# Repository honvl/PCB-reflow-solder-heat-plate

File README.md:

# PCB reflow solder heat plate

## Introduction

The PCB reflow solder heat plate can be used to solder small PCBs with SMD parts. The user can control the maximum temperature and heating curve. Buy a pre-assembled version here: https://www.tindie.com/products/littlethings/pcb-reflow-soldering-hot-plate/

## Hardware design

The idea for this design comes from https://github.com/AfterEarthLTD/Solder-Reflow-Plate. But when I checked the original design, I found some issues that could cause safety problems and other design choices that are not optimal.

## Hardware version 1.2

- Removed resettable fuse which was overheating and tripping
- Increased power supply capacitor ratings to 35V for 24V power supply compatibility
- Use 2 SMD capacitors for power supply capacitors instead of 4 standard ones for lower total board height
- Changed to easier to press switches

### Feature list

- PCB size 100x100mm, heat plate size 81x69mm
- DC barrel plug (5.5x2.5mm), runs with 12V/5A power supply
- inrush current limiter to protect power supply when capacitors are discharged
- 2.7mF input power filter for smooth current draw
- capacitor discharging resistors
- ATMEGA4809 MCU, can be programmed via UPDI header
- high power NMOS with gate driver circuit
- flyback diode connected to the heat plate
- AMS1117 LDO
- additional diodes for protection
- dual buttons
- status LED
- 0.91" OLED display
- LMT85 analog temperature sensor as main sensor
- option to add additional digital sensors for calibration purposes

### Building your own

You can order almost all parts needed from LCSC/JLCPCB. Only the OLED display and the power supply need to be sourced elsewhere. The BOM includes LCSC part numbers for hand soldering and their automated SMT manufacturing. Minimal part size is 0805 and there's enough space between all solder pads, so hand soldering should be no problem if you have a steady hand. Hardest part will be the MCU, but this is hand solderable, too.

### Safety measures compared to the original design

The original design had a too low heat plate resistance, which caused very high current spikes when the heat plate was turned on. This should be filtered by PWM and the input capacitors, but the input capacitor in the original design was far too small (100µF). Because of this, the fuse always blew when the device was turned on, so eventually the fuse was removed again.
In my design I made the input capacitors 27 times larger to have a smoother current draw. I also added a fuse, and an inrush current limiter. After disconnecting the power supply, the output capacitors are quickly discharged to GND.
The original also had no gate driver, so the NMOS was only driven with logic levels. I added a simple NPN gate driver.
Switching inductive loads (like the long heat plate trace) causes voltage spikes. In the original design, the filtering was done with an ESD diode and a small capacitor. The usual way to filter these voltage spikes is a flyback diode.
The resistance of the heat plate was very low, so the current draw with 100% PWM duty cycle was very high. If the MCUs hangs up and the power MOSFET stays active, the original design could cause too much stress for the power supply. Furthermore, even with a hot heat plate, the resistance would still be so low that the board would draw more than 5A.
In my design, the heat plate resistance was chosen in a way that a hot heat plate will draw less than 5A, so it is much safer to run the new design, as it will automatically reach electrically safe working conditions.

## Firmware

The original firmware was reworked by Nathan Heidt (https://github.com/heidtn) and works mostly, only the temperature sensing is incorrect (as the firmware was written with an earlier board revision). So for now, you just need to unplug the device when the PCB that needed soldering is done. Also, the dual color LED is not yet included into the code, for now it just lights green to show power. And the buttons sometimes don't react properly.

Daniel Oltmanns (https://github.com/oltdaniel) is doing a rework of the firmware using platformio.

### To-do list for software:
- use of the dual color LED (green = power, orange = heating, red = hot)
- better temperature sensing
- better working buttons
- calibration function for the analog temperature sensor by taping a digital probe directly to the heat plate

Please note that I can only do hardware design, so I can't contribute anything to the software. 

### Programming the MCU

The MCU can be programmed with JTAG2UPDI (https://github.com/ElTangas/jtag2updi). For programming, you need an Arduino with ATMEGA328p (Uno or Nano), some wires, a 4.7k resistor and  a 10µF capacitor or 120 Ohm resistor to disable the auto-reset.

JCM from the Discord explained the process pretty good:

> 1. Download/Clone this project: https://github.com/ElTangas/jtag2updi and rename the folder "source" to "jtag2updi" (otherwise the Arduino IDE won't like it)
> 2. Open jtag2updi/jtag2updi.ino in your Arduino IDE
> 3. Configure the flasher options for your Arduino Nano and flash it
> 4. Connect D6 of your Arduino Nano over the 4.7kOhm resistor to the UPDI pin of the board and 5V to 5V and GND to 0V
> 5. Add the MegaCoreX hardware package to the Ardunio IDE (see https://github.com/MCUdude/MegaCoreX#how-to-install)
> 6. Install the Adafruit_GFX, Adafruit_SSD1306, DallasTemperature and Debounce2 libraries with the Library Manager (you might not need all of them depending on which firmware you plan to use)
> 7. Download and open the ino you want to upload to the ATMEGA4809 (https://github.com/DerSpatz/PCB-reflow-solder-heat-plate/blob/main/Firmware/pcb_reflow_fw/pcb_reflow_fw.ino)
> 8. Select the options for the programmer (Board: ATmega4809, Clock: Internal 16 MHz, BOD: 2.6V or 2.7V, EEPROM: retained, Pinout: 48 pin standard, Reset pin: Reset, no Bootloader) and select the port of your Ardunio Nano as Port
> 9. Select Burn Bootloader and see if it runs through
> 10. Temporarily disable auto reset for the Arduino Nano: https://playground.arduino.cc/Main/DisablingAutoResetOnSerialConnection/ (not sure if it's needed for the Nano, it was for my Mega)
> 11. Select Sketch > Upload using Programmer (normal Upload will not work)

## Thanks

Special Thanks go out to:

Nathan Heidt for writing the software and testing

Merlin Shaw (www.facebook.com/GeekIslandGaming) for ordering the first batch of prototypes and testing

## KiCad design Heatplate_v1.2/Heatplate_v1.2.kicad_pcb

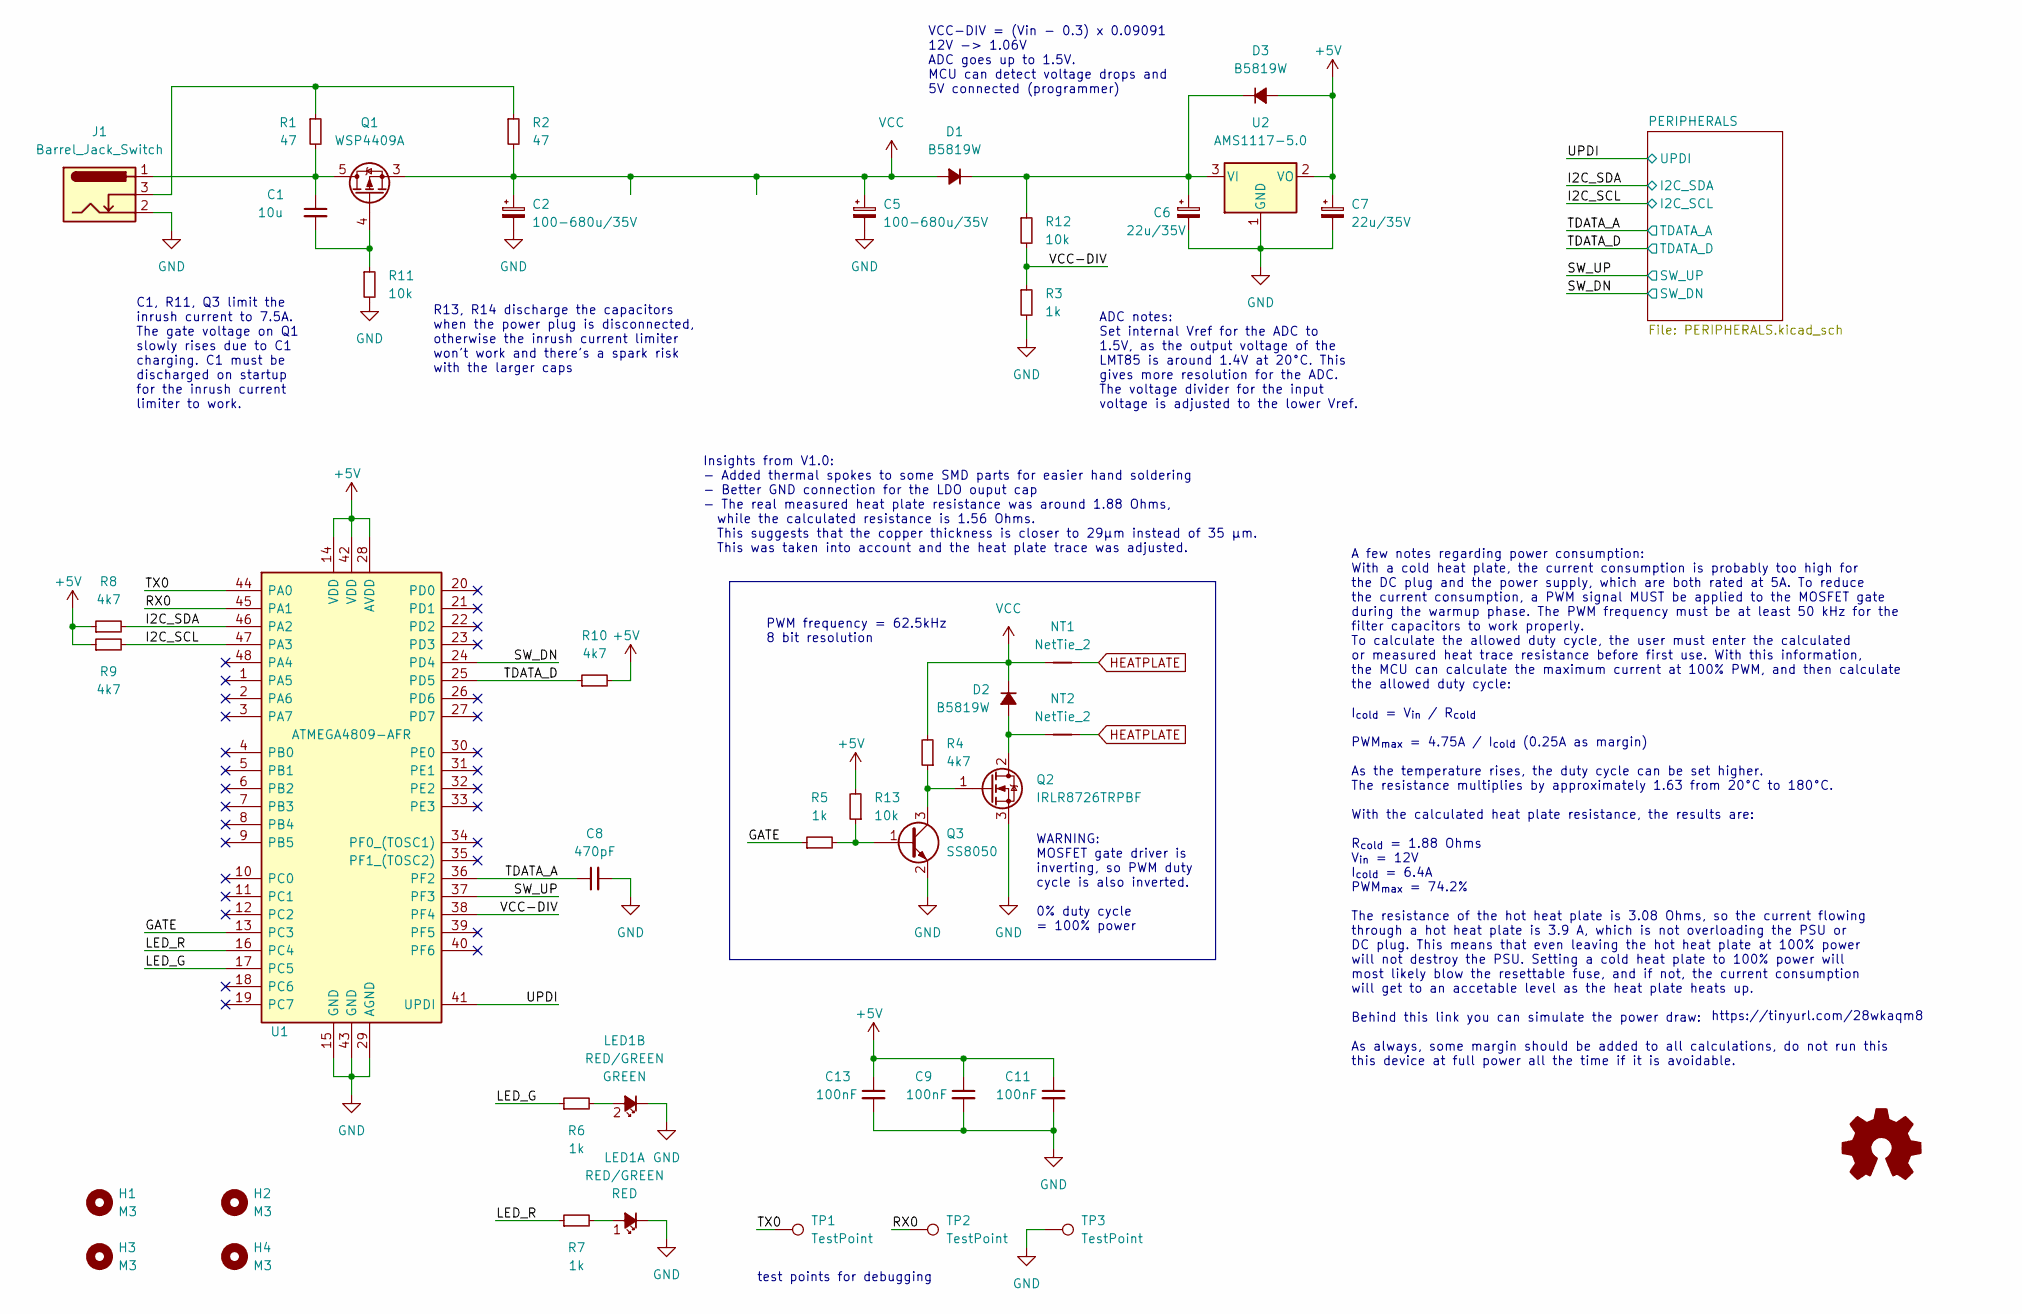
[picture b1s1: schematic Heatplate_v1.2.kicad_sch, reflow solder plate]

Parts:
C1: 10u; C_0805_2012Metric; LCSC Part Number C162422
C2, C5: 100-680u/35V; CP_Elec_8x10; LCSC Part Number C882163
C6, C7: 22u/35V; CP_Elec_5x5.4; LCSC Part Number C239256
C8: 470pF; C_0805_2012Metric; LCSC Part Number C1743
C9, C11, C13: 100nF; C_0805_2012Metric; LCSC Part Number C1711
D1, D2, D3: B5819W; D_SOD-123; LCSC Part Number C64885
H1, H2, H3, H4: M3; MountingHole_3.2mm_M3; LCSC Part Number C551332
J1: Barrel_Jack_Switch; BarrelJack_Horizontal; LCSC Part Number C381115
LED1: RED/GREEN; LED_Avago_PLCC4_3.2x2.8mm_CW; LCSC Part Number C131251
LOGO1: Logo_Open_Hardware_Small; OSHW-Logo2_7.3x6mm_SilkScreen
NT1, NT2: NetTie_2; NetTie-2_SMD_Pad1.3mm
Q1: WSP4409A; SOIC-8_3.9x4.9mm_P1.27mm; LCSC Part Number C2880527
Q2: IRLR8726TRPBF; TO-252-2; LCSC Part Number C81137
Q3: SS8050; SOT-23; LCSC Part Number C444722
R1, R2: 47; R_0805_2012Metric; LCSC Part Number C17714
R3, R5, R6, R7: 1k; R_0805_2012Metric; LCSC Part Number C17513
R4, R8, R9, R10: 4k7; R_0805_2012Metric; LCSC Part Number C17673
R11, R12, R13: 10k; R_0805_2012Metric; LCSC Part Number C17414
TP1, TP2, TP3: TestPoint; TestPoint_Pad_D1.5mm
U1: ATMEGA4809-AFR; TQFP-48_7x7mm_P0.5mm; Manufacturer_Part_Number ATMEGA4809-AFR; Mouser Part Number 556-ATMEGA4809-AFR
U2: AMS1117-5.0; SOT-89-3; LCSC Part Number C351450

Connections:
+5V: C7.1, C9.1, C11.1, C13.1, D3.2 (A), R8.1, R9.1, R10.2, R13.2, U1.14 (VDD), U1.28 (AVDD), U1.42 (VDD), U2.2 (VO); also elsewhere on the board
/GATE: R5.1, U1.13 (PC3)
/I2C_SCL: R9.2, U1.47 (PA3); also elsewhere on the board
/I2C_SDA: R8.2, U1.46 (PA2); also elsewhere on the board
/LED_G: R6.1, U1.17 (PC5)
/LED_R: R7.1, U1.16 (PC4)
/RX0: TP2.1, U1.45 (PA1)
/SW_DN: U1.24 (PD4); also elsewhere on the board
/SW_UP: U1.37 (PF3); also elsewhere on the board
/TDATA_A: C8.1, U1.36 (PF2); also elsewhere on the board
/TDATA_D: R10.1, U1.25 (PD5); also elsewhere on the board
/TX0: TP1.1, U1.44 (PA0)
/UPDI: U1.41 (UPDI); also elsewhere on the board
/VCC-DIV: R3.1, R12.2, U1.38 (PF4)
GND: C2.2, C5.2, C6.2, C7.2, C8.2, C9.2, C11.2, C13.2, J1.2, LED1.2 (K1), LED1.4 (K2), Q2.3 (S), Q3.2 (E), R3.2, R11.2, TP3.1, U1.15 (GND), U1.29 (AGND), U1.43 (GND), U2.1 (GND); also elsewhere on the board
HEATPLATE: NT1.2, NT2.2
unnamed: C1.1, J1.1, Q1.5 (D), Q1.6 (D), Q1.7 (D), Q1.8 (D), R1.2
unnamed: C6.1, D1.1 (K), D3.1 (K), R12.1, U2.3 (VI)
unnamed: D2.2 (A), NT2.1, Q2.2 (D)
unnamed: J1.3, R1.1, R2.1
unnamed: LED1.1 (A1), R7.2
unnamed: LED1.3 (A2), R6.2
unnamed: C1.2, Q1.4 (G), R11.1
unnamed: Q2.1 (G), Q3.3 (C), R4.1
unnamed: Q3.1 (B), R5.2, R13.1
VCC: C2.1, C5.1, D1.2 (A), D2.1 (K), NT1.1, Q1.1 (S), Q1.2 (S), Q1.3 (S), R2.2, R4.2

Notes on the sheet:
C1, R11, Q3 limit the inrush current to 7.5A. The gate voltage on Q1 slowly rises due to C1 charging. C1 must be discharged on startup for the inrush current limiter to work.
VCC-DIV = (Vin - 0.3) x 0.09091 12V -> 1.06V ADC goes up to 1.5V. MCU can detect voltage drops and 5V connected (programmer)
PWM frequency = 62.5kHz 8 bit resolution
A few notes regarding power consumption: With a cold heat plate, the current consumption is probably too high for the DC plug and the power supply, which are both rated at 5A. To reduce the current consumption, a PWM signal MUST be applied to the MOSFET gate during the warmup phase. The PWM frequen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
WARNING: MOSFET gate driver is inverting, so PWM duty cycle is also inverted. 0% duty cycle = 100% power
R13, R14 discharge the capacitors when the power plug is disconnected, otherwise the inrush current limiter won't work and there's a spark risk with the larger caps
https://tinyurl.com/28wkaqm8
test points for debugging
ADC notes: Set internal Vref for the ADC to 1.5V, as the output voltage of the LMT85 is around 1.4V at 20°C. This gives more resolution for the ADC. The voltage divider for the input voltage is adjusted to the lower Vref.
Insights from V1.0: - Added thermal spokes to some SMD parts for easier hand soldering - Better GND connection for the LDO ouput cap - The real measured heat plate resistance was around 1.88 Ohms, while the calculated resistance is 1.56 Ohms. This suggests that the copper thickness is closer to 29µ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

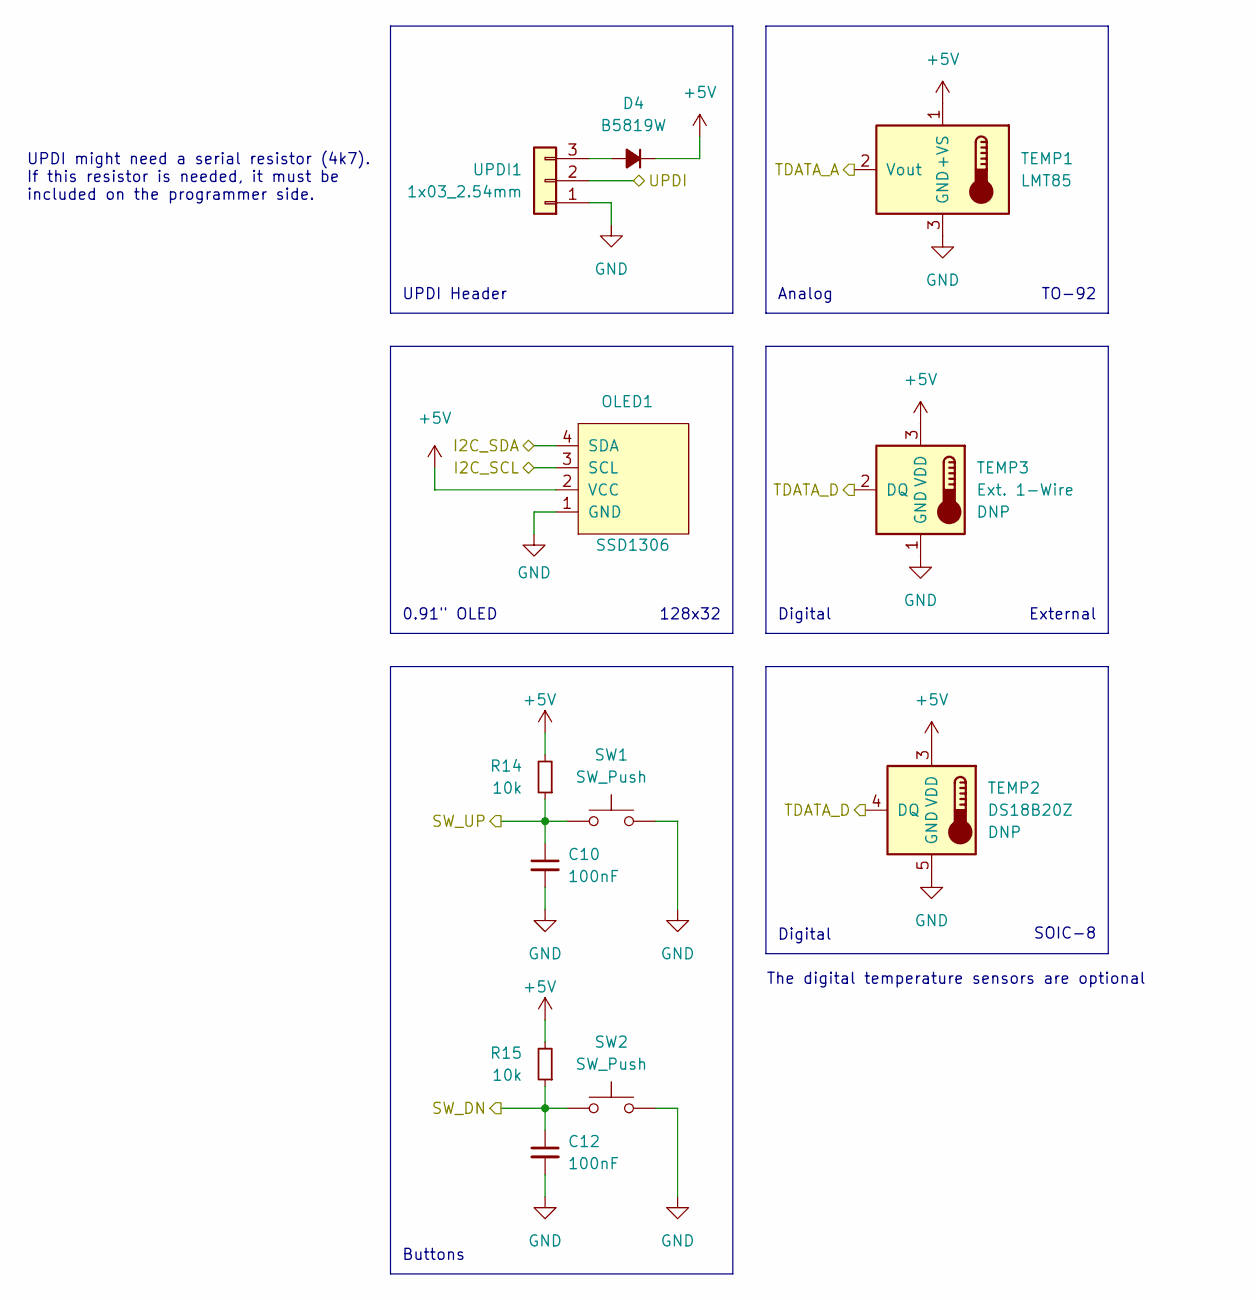
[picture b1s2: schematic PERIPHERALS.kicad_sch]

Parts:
C10, C12: 100nF; C_0805_2012Metric; LCSC Part Number C1711
D4: B5819W; D_SOD-123; LCSC Part Number C64885
OLED1: SSD1306; 0.91Inch-OLED-Module; LCSC Part Number C2718488
R14, R15: 10k; R_0805_2012Metric; LCSC Part Number C17414
SW1, SW2: SW_Push; SW_PUSH_6mm; LCSC Part Number C93151
TEMP1: LMT85; TO-92_Inline; LCSC Part Number C75856
TEMP2: DS18B20Z; SOIC-8_3.9x4.9mm_P1.27mm; LCSC Part Number C695837
TEMP3: Ext. 1-Wire; PinHeader_1x03_P2.54mm_Vertical
UPDI1: 1x03_2.54mm; PinHeader_1x03_P2.54mm_Vertical; LCSC Part Number C49257

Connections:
+5V: D4.1 (K), OLED1.2 (VCC), R14.2, R15.2, TEMP1.1 (+VS), TEMP2.3 (VDD), TEMP3.3 (VDD); also elsewhere on the board
/I2C_SCL: OLED1.3 (SCL); also elsewhere on the board
/I2C_SDA: OLED1.4 (SDA); also elsewhere on the board
/SW_DN: C12.1, R15.1, SW2.1; also elsewhere on the board
/SW_UP: C10.1, R14.1, SW1.1; also elsewhere on the board
/TDATA_A: TEMP1.2 (Vout); also elsewhere on the board
/TDATA_D: TEMP2.4 (DQ), TEMP3.2 (DQ); also elsewhere on the board
/UPDI: UPDI1.2; also elsewhere on the board
GND: C10.2, C12.2, OLED1.1 (GND), SW1.2, SW2.2, TEMP1.3 (GND), TEMP2.5 (GND), TEMP3.1 (GND), UPDI1.1; also elsewhere on the board
unnamed: D4.2 (A), UPDI1.3

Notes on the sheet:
SOIC-8
Digital
UPDI Header
128x32
Analog
TO-92
0.91" OLED
The digital temperature sensors are optional
Buttons
UPDI might need a serial resistor (4k7). If this resistor is needed, it must be included on the programmer side.
External

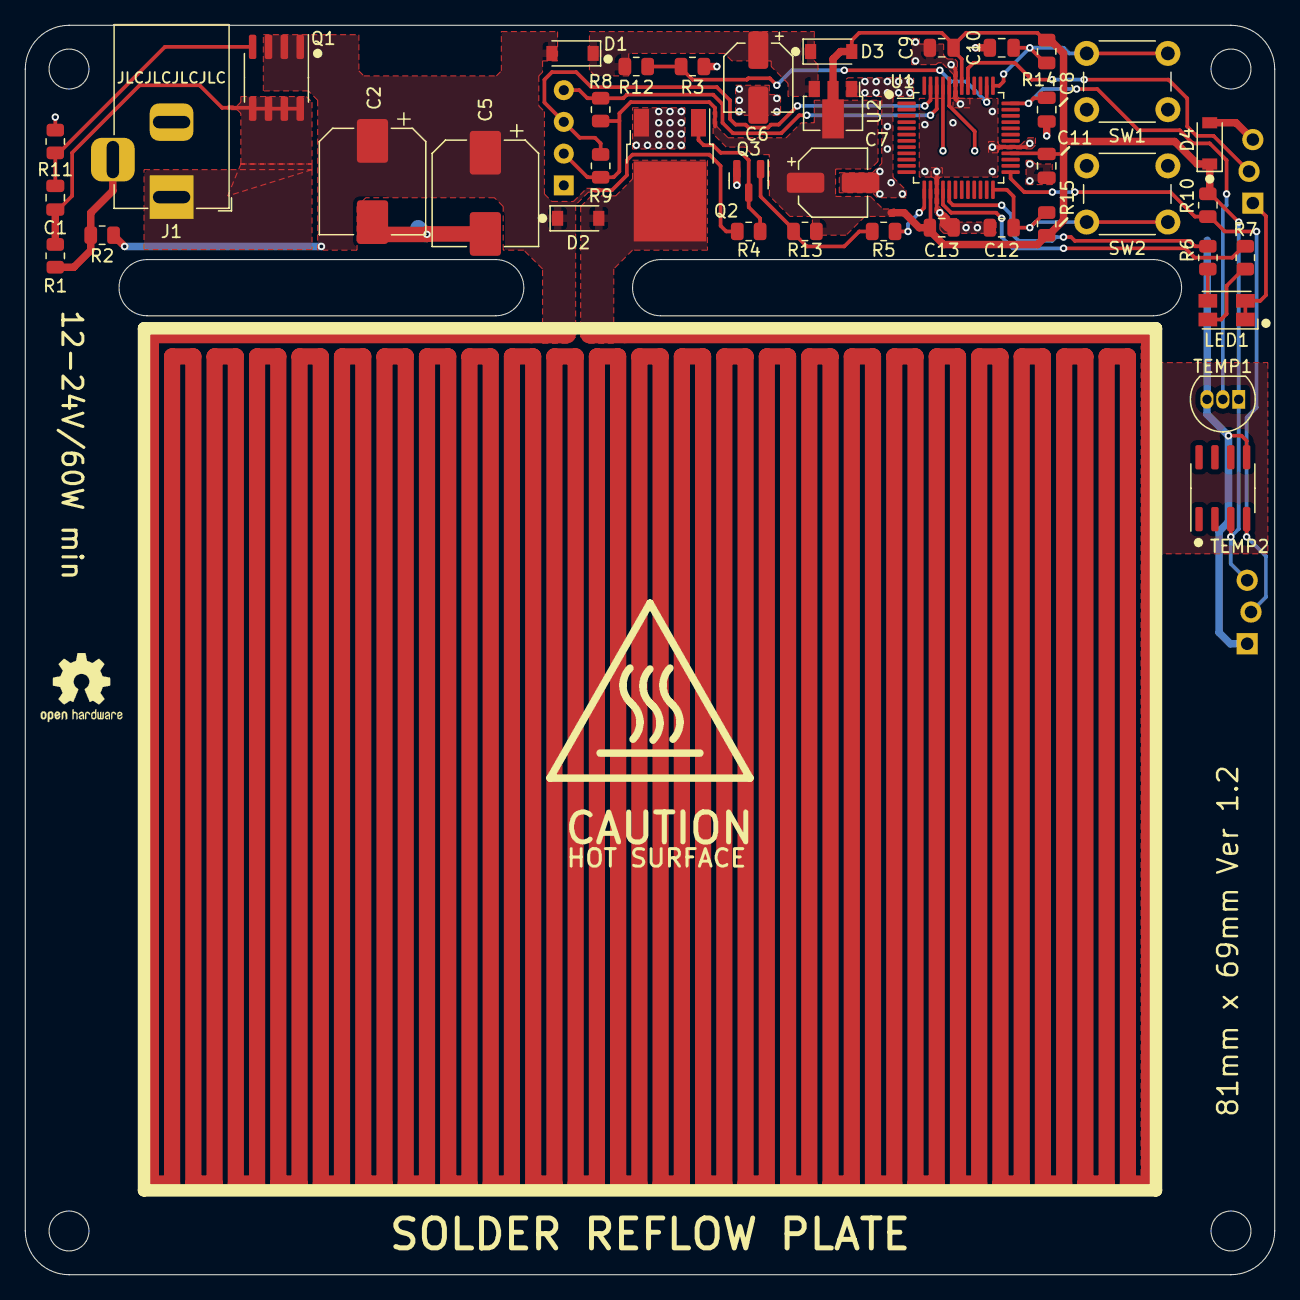
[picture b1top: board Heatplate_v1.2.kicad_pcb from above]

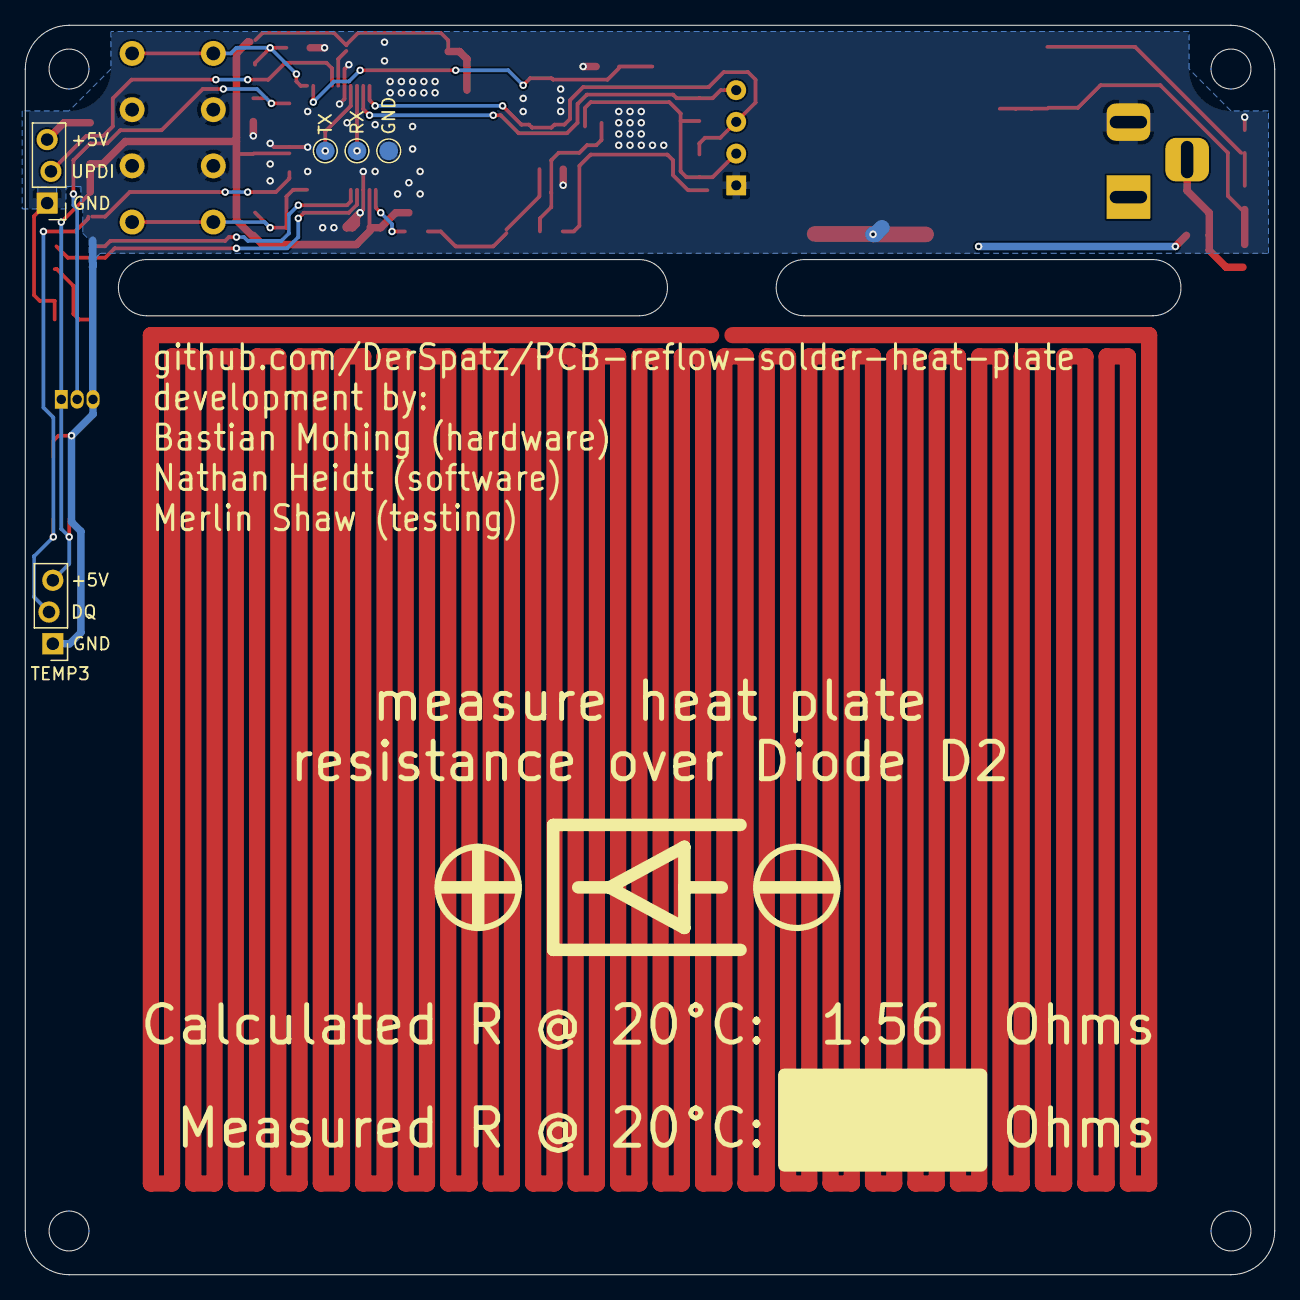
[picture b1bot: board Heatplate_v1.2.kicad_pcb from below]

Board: 2 copper layers, 100.0 x 100.0 mm, 54 parts (5 on the bottom side), 27 nets.

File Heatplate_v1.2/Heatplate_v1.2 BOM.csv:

"null","Sourced","Placed","References","Value","Footprint","Assembly","LCSC Part Number","Description","Quantity"
1,"","","C9, C10, C11, C12, C13","100nF","C_0805_2012Metric","","C1711","Unpolarized capacitor, small symbol",5
2,"","","C2, C5","100-680u/35V","CP_Elec_8x10","","C442884","Polarized capacitor, small symbol",2
3,"","","C6, C7","22u/35V","CP_Elec_5x5.4","","C239256","Polarized capacitor, small symbol",2
4,"","","C1","10u","C_0805_2012Metric","","C162422","Unpolarized capacitor, small symbol",1
5,"","","C8","470pF","C_0805_2012Metric","","C1743","Unpolarized capacitor, small symbol",1
6,"","","R11, R12, R13, R14, R15","10k","R_0805_2012Metric","","C17414","Resistor, small symbol",5
7,"","","R3, R5, R6, R7","1k","R_0805_2012Metric","","C17513","Resistor, small symbol",4
8,"","","R4, R8, R9, R10","4k7","R_0805_2012Metric","","C17673","Resistor, small symbol",4
9,"","","R1, R2",47,"R_0805_2012Metric","","C17714","Resistor, small symbol",2
10,"","","D1, D2, D3, D4","B5819W","D_SOD-123","","C64885","Diode, small symbol, filled shape",4
11,"","","U1","ATMEGA4809-AFR","TQFP-48_7x7mm_P0.5mm","","C189475","MICROCHIP - ATMEGA4809-AFR - MCU, 8BIT, ATMEGA, 20MHZ, TQFP-48",1
12,"","","U2","AMS1117-5.0","SOT-89-3","","C351450","1A Low Dropout regulator, positive, 5.0V fixed output, SOT-223",1
13,"","","SW1, SW2","SW_Push","SW_PUSH_6mm","","C93151","Push button switch, generic, two pins",2
14,"","","H1, H2, H3, H4","M3","MountingHole_3.2mm_M3","","C551332","Mounting Hole without connection",4
15,"","","LED1","RED/GREEN","LED_Avago_PLCC4_3.2x2.8mm_CW","","C131251","Light emitting diode, small symbol, filled shape",1
16,"","","OLED1","SSD1306","0.91Inch-OLED-Module","","C2718488","SSD1306 OLED",1
17,"","","Q1","WSP4409A","SOIC-8_3.9x4.9mm_P1.27mm","","C2880527","N-MOSFET transistor, drain/gate/source",1
18,"","","Q2","IRLR8726TRPBF","TO-252-2","","C81137","N-MOSFET transistor, gate/drain/source",1
19,"","","Q3","SS8050","SOT-23","","C444722","NPN transistor, base/emitter/collector",1
20,"","","TEMP1","LMT85","TO-92_Inline","","C75856","Precision centigrade temperature sensor, TO-92",1
21,"","","J1","Barrel_Jack_Switch","BarrelJack_Horizontal","","C381115","DC Barrel Jack with an internal switch",1

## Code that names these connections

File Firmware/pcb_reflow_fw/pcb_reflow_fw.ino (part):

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Adafruit_SSD1306 display(SCREEN_WIDTH, SCREEN_HEIGHT, &Wire, -1); // Create Display

// Pin Definitions
#define MOSFET_PIN PIN_PC3
#define UPSW_PIN PIN_PF3
#define DNSW_PIN PIN_PD4
#define TEMP_PIN PIN_PF2 // A2
#define VCC_PIN PIN_PF4  // A0
#define LED_GREEN_PIN PIN_PC5
#define LED_RED_PIN PIN_PC4
#define ONE_WIRE_BUS PIN_PD5

#define MOSFET_PIN_OFF 255

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
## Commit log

2023-05-09 Add files via upload
    Changed so that it no longer causes 12V 5A supply to reset
2023-05-09 Update pcb_reflow_fw.ino
    Adjust PWM conditions after overshoot
2023-06-08 test
2023-06-08 Add BOM
2023-06-08 interactive bom
2023-06-09 ibom
